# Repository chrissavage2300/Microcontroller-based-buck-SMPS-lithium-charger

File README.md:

# Microcontroller-based-buck-SMPS-lithium-charger
PIC18F13K22 Based lithium buck coverter

Based on app note SLAA-287-Li-Ion Battery Charger Solution Using an MSP430™ MCU from Texas Instruments. 

Note: U2, JP3 and R5 are not used. The internal VREF is used.

JP6/7 have been replaced with 1206 LEDs

R6-50ohms may work rather than 0.

JP5 limits the input voltage to 5V, so IC1 wouldnt need to be populated in this case. It therefore may also work off of a USB-C connector but this hasnt been tested. 

Pins RC1 and RC2 are not used even though they are called out.

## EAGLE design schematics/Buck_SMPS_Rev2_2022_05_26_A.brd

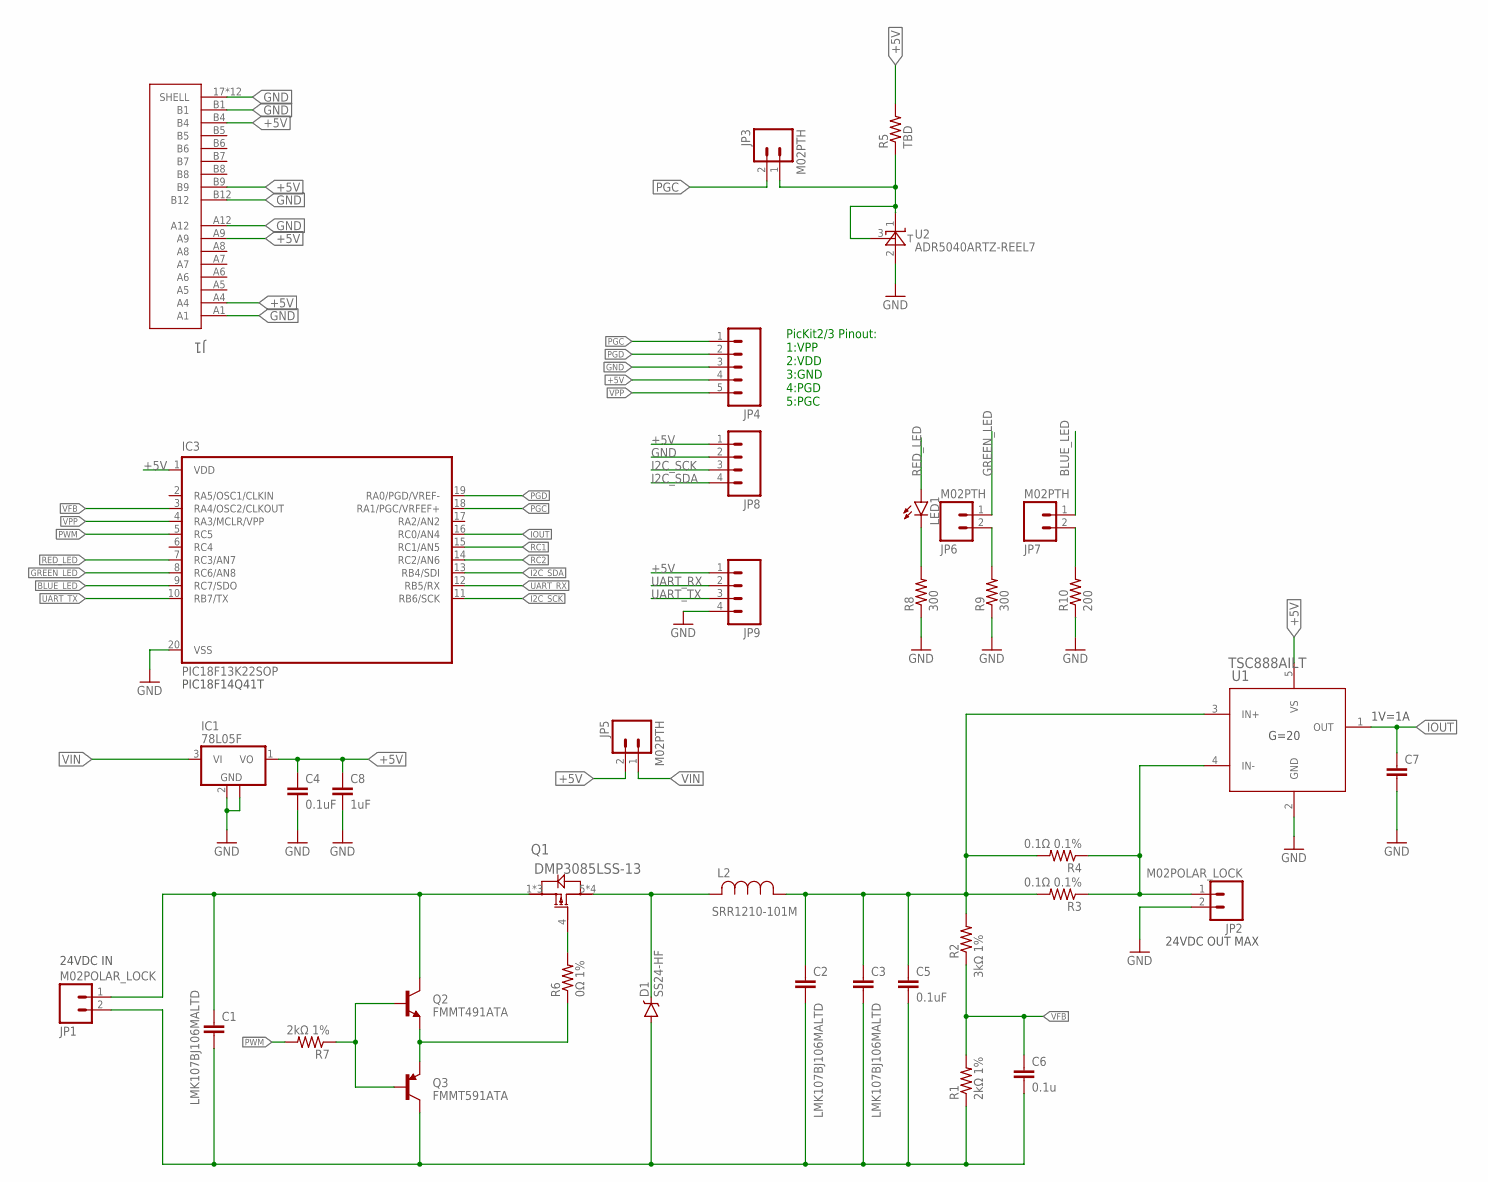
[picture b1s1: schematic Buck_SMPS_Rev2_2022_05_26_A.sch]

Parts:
C1, C2, C3: LMK107BJ106MALTD; 1206
C4, C5: 0.1uF; 1206
C6: 0.1u; 0805
C7: CAP0805; 0805
C8: 1uF; 1206
D1: SS24-HF; SMA-DIODE
IC1: 78L05F; SOT89
IC3: PIC18F13K22SOP; SOP20W
J1: USB4085-GF-A; CONN16_USB4085-GF-A_GCT
JP1, JP2: M02POLAR_LOCK; MOLEX-1X2_LOCK
JP3, JP5, JP6, JP7: M02PTH; 1X02
JP4: M05PTH_LONGPADS; 1X05_LONGPADS
JP8, JP9: M04LOCK; 1X04_LOCK
L2: SRR1210-101M; IND_BOURNS_SRR1210
LED1: LED1206; LED-1206
Q1: DMP3085LSS-13; IC_DMP3085LSS-13_DIO-M
Q2: FMMT491ATA; SOT23
Q3: FMMT591ATA; SOT23
R1, R7: 2kΩ 1%; 1206
R2: 3kΩ 1%; 1206
R3, R4: 0.1Ω 0.1%; 1206
R5: TBD; 1206
R6: 0Ω 1%; 1206
R8, R9: 300; 1206
R10: 200; 1206
U1: TSC888AILT; DBV0005A_N
U2: ADR5040ARTZ-REEL7; RT_3_ADI

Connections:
+5V: C4.1, C8.1, IC1.1 (VO), IC3.1 (VDD), J1.A4, J1.A9, J1.B4, J1.B9, JP4.4, JP5.2, JP8.1, JP9.1, R5.2, U1.5 (VS)
BLUE_LED: IC3.9 (RC7/SDO), JP7.1
GND: C1.2, C2.2, C3.2, C4.2, C5.2, C6.2, C7.2, C8.2, D1.A, IC1.2 (GND), IC1.2@1 (GND), IC3.20 (VSS), J1.17 (SHELL), J1.18 (SHELL), J1.19 (SHELL), J1.20 (SHELL), J1.21 (SHELL), J1.22 (SHELL), J1.23 (SHELL), J1.24 (SHELL), J1.25 (SHELL), J1.26 (SHELL), J1.27 (SHELL), J1.28 (SHELL), J1.A1, J1.A12, J1.B1, J1.B12, JP1.2, JP2.2, JP4.3, JP8.2, JP9.4, Q3.3 (C), R1.1, R8.1, R9.1, R10.1, U1.2 (GND), U2.2 (A)
GREEN_LED: IC3.8 (RC6/AN8), JP6.1
I2C_SCK: IC3.11 (RB6/SCK), JP8.3
I2C_SDA: IC3.13 (RB4/SDI), JP8.4
IOUT: C7.1, IC3.16 (RC0/AN4), U1.1 (OUT)
unnamed: LED1.C, R8.2
unnamed: Q2.2 (E), Q3.2 (E), R6.1
unnamed: JP6.2, R9.2
unnamed: JP7.2, R10.2
unnamed: Q1.4 (G), R6.2
unnamed: Q2.1 (B), Q3.1 (B), R7.1
PGC: IC3.18 (RA1/PGC/VRFEF+), JP3.2, JP4.1
PGD: IC3.19 (RA0/PGD/VREF-), JP4.2
PWM: IC3.5 (RC5), R7.2
RC1: IC3.15 (RC1/AN5)
RC2: IC3.14 (RC2/AN6)
RED_LED: IC3.7 (RC3/AN7), LED1.A
SW: D1.C, L2.2, Q1.5 (D), Q1.6 (D), Q1.7 (D), Q1.8 (D)
UART_RX: IC3.12 (RB5/RX), JP9.2
UART_TX: IC3.10 (RB7/TX), JP9.3
VFB: C6.1, IC3.3 (RA4/OSC2/CLKOUT), R1.2, R2.1
VIN: C1.1, IC1.3 (VI), JP1.1, JP5.1, Q1.1 (S), Q1.2 (S), Q1.3 (S), Q2.3 (C)
VOUT: C2.1, C3.1, C5.1, L2.1, R2.2, R3.2, R4.2, U1.3 (IN+)
VOUT+: JP2.1, R3.1, R4.1, U1.4 (IN-)
VPP: IC3.4 (RA3/MCLR/VPP), JP4.5
VREF+: JP3.1, R5.1, U2.1 (C), U2.3 (T)

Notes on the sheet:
PicKit2/3 Pinout: 1:VPP 2:VDD 3:GND 4:PGD 5:PGC
24VDC IN
24VDC OUT MAX
G=20
1V=1A
PIC18F14Q41T

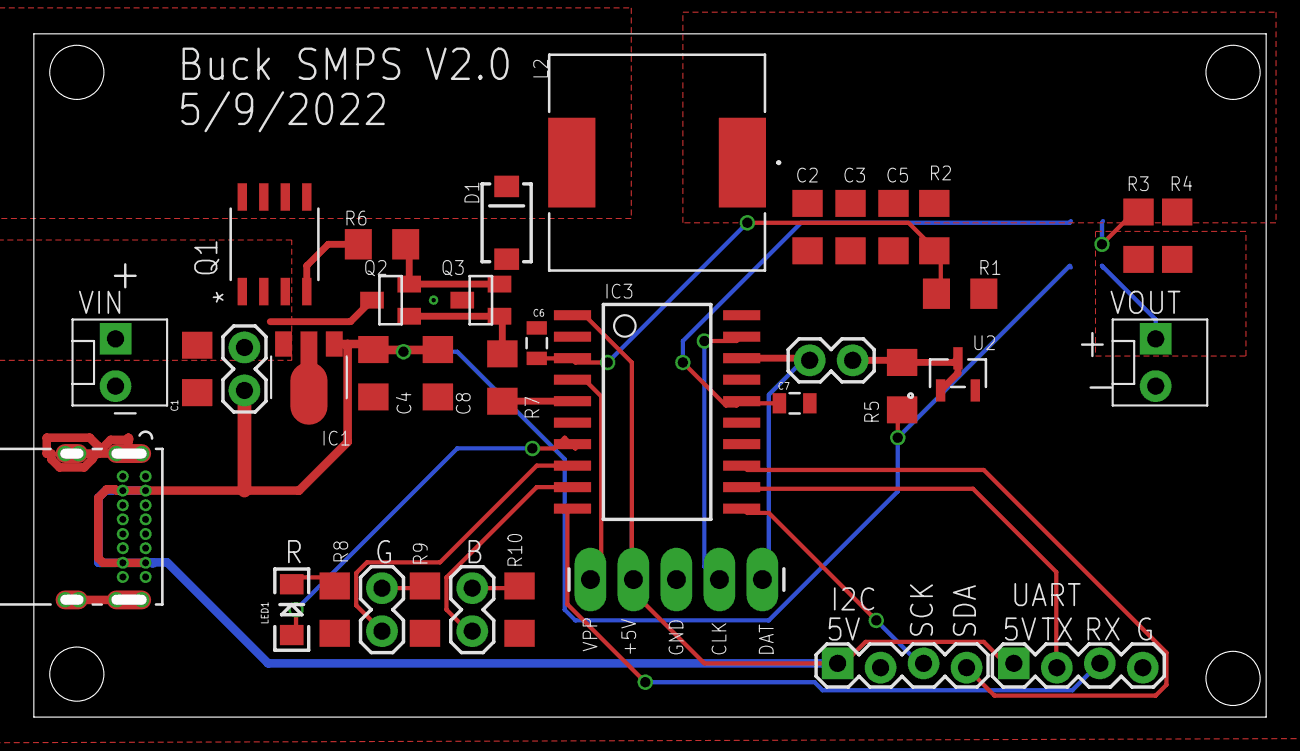
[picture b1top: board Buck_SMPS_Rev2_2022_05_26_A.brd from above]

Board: 2 copper layers, 72.2 x 39.8 mm, 38 parts (1 on the bottom side), 26 nets.

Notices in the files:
parts and their libraries:
SparkFun-DiscreteSemi: Licensing: Creative Commons ShareAlike 4.0 International - https://creativecommons.org/licenses/by-sa/4.0
COPYRIGHT: Copyright (C) 2021 Ultra Librarian. All rights reserved.
COPYRIGHT: Copyright (C) 2022 Ultra Librarian. All rights reserved.
